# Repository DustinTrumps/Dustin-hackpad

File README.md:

</head>
<body>

<h1>Full Hackpad – 12 Key Macro Pad with Encoder(ok that was a bit rude from me sorry,but thanks for having me remake the full asmbaly it shouwd me that i had to remake my pcb and cad)</h1>
<div>
<h2>All Images</h2>
<table>
<tr>
    <th>Image</th>
    <th>Description</th>
</tr>
<tr>
    <td></td>
    <td>Full Hackpad CAD model</td>
</tr>
<tr>
    <td></td>
    <td>Board schematic</td>
</tr>
<tr>
    <td></td>
    <td>PCB layout</td>
</tr>
<tr>
    <td></td>
    <td>Fitment / assembly test</td>
</tr>
</table>
</div>

<div>
<h2>Firmware Overview</h2>
<p>The code is designed to be a configurable macropad. Each key can be assigned to shortcuts, macros, or other functions.</p>
<ul>
    <li>Rotary encoder for <strong>volume control</strong>.</li>
</ul>
</div>

<div>
<h2>Bill of Materials (BOM)</h2>
<table>
<tr>
    <th>Component</th>
    <th>Quantity</th>
    <th>Notes</th>
</tr>
<tr><td>10K Resistor</td><td>2</td><td>i will Provid</td></tr>
<tr><td>Rotary Encoder w/ Push Button</td><td>1</td><td>If the one you ship dose not have a Switch, i will Provid it</td></tr>
<tr><td>Cherry MX Switches</td><td>12</td><td></td></tr>
<tr><td>DSA Keycaps</td><td>12</td><td></td></tr>
<tr><td>M3x5x4 Heat-set Inserts</td><td>4</td><td></td></tr>
<tr><td>M3x12mm SHCS Bolts</td><td>4</td><td></td></tr>
<tr><td>Seeed XIAO RP2040</td><td>1</td><td></td></tr>
<tr><td>PCB</td><td>1</td><td></td></tr>
<tr><td>1 by 7 male header pins</td><td>2</td><td></td></tr>
<tr><td>3D Printed Case (2 parts)</td><td>1 Set</td><td>Hackpad bottom +Hackpad top , 3d print files in CAD/3D PRINTED PARTS</td></tr>
</table>
</div>

<div>
<h2>Assembly Steps</h2>
<ol>
    <li>Install <strong>heat-set brass inserts</strong>.</li>
    <li>Solder switches, encoder, and other components.</li>
    <li>Attach <strong>XIAO RP2040</strong> to PCB.</li>
    <li>Flash firmware.</li>
    <li>Assemble the case using screws.</li>
    <li>Install keycaps./li>
</ol>
</div>
</body>
</html>

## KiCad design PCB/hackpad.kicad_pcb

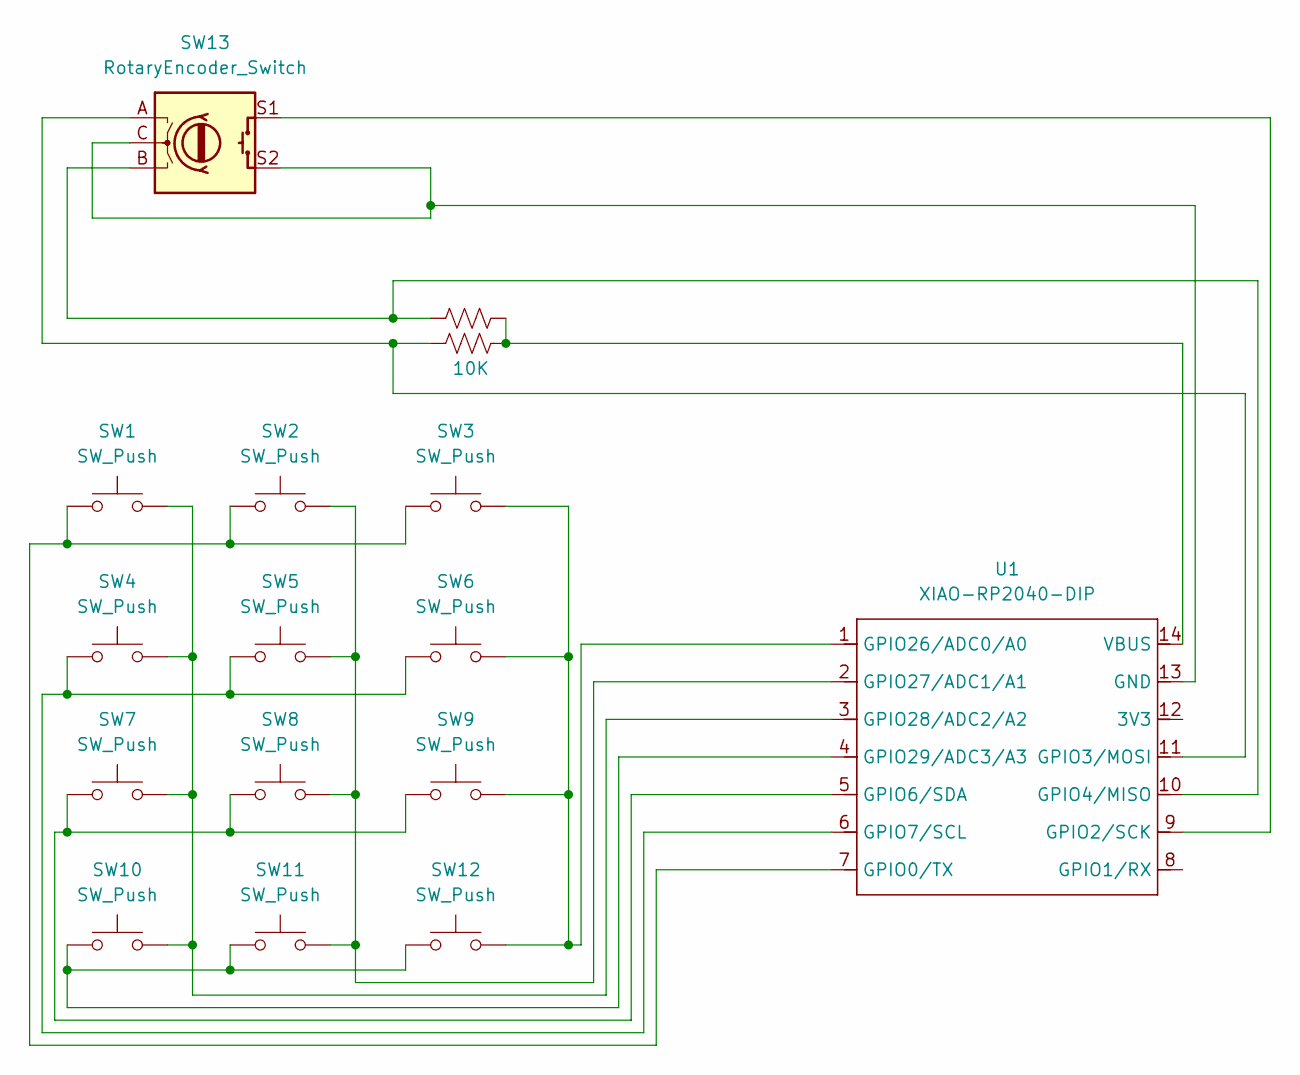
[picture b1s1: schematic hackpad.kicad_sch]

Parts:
R1: 10K; R_Axial_DIN0207_L6.3mm_D2.5mm_P10.16mm_Horizontal
R2: R_US; R_Axial_DIN0207_L6.3mm_D2.5mm_P10.16mm_Horizontal
SW1, SW2, SW3, SW5, SW6, SW8, SW9, SW10, SW11, SW12: SW_Push; SW_Cherry_MX_1.00u_PCB
SW4, SW7: SW_Push; SW_Cherry_MX_1.00u_Plate
SW13: RotaryEncoder_Switch; RotaryEncoder_Alps_EC11E-Switch_Vertical_H20mm
U1: XIAO-RP2040-DIP

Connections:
unnamed: SW13.C, SW13.S2, U1.13 (GND)
unnamed: SW1.1, SW2.1, SW3.1, U1.7 (GPIO0/TX)
unnamed: SW13.S1, U1.9 (GPIO2/SCK)
unnamed: R1.1, SW13.A, U1.11 (GPIO3/MOSI)
unnamed: R2.1, SW13.B, U1.10 (GPIO4/MISO)
unnamed: SW7.1, SW8.1, SW9.1, U1.5 (GPIO6/SDA)
unnamed: SW4.1, SW5.1, SW6.1, U1.6 (GPIO7/SCL)
unnamed: SW3.2, SW6.2, SW9.2, SW12.2, U1.1 (GPIO26/ADC0/A0)
unnamed: SW2.2, SW5.2, SW8.2, SW11.2, U1.2 (GPIO27/ADC1/A1)
unnamed: SW1.2, SW4.2, SW7.2, SW10.2, U1.3 (GPIO28/ADC2/A2)
unnamed: SW10.1, SW11.1, SW12.1, U1.4 (GPIO29/ADC3/A3)
unnamed: R1.2, R2.2, U1.14 (VBUS)

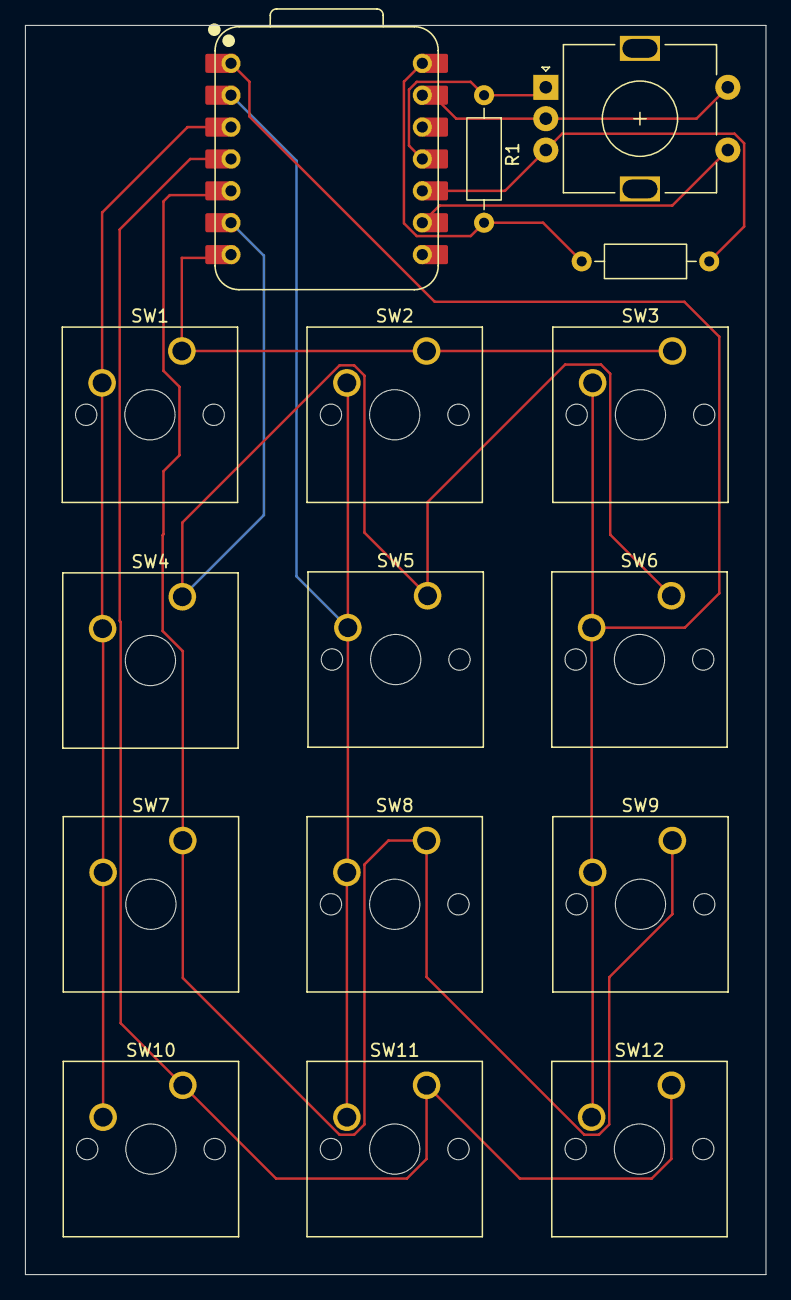
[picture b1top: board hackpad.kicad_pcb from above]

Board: 2 copper layers, 59.0 x 99.5 mm, 16 parts (0 on the bottom side), 12 nets.

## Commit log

2025-12-07 inital comit
2025-12-07 reabme.mb update
2025-12-07 updt
